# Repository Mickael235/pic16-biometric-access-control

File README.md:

# PIC16 Biometric Access Control

<p align="center">
  <strong>Biometric access-control system combining embedded electronics, PCB design and parametric mechanical integration</strong><br>
  PIC16F88 · SFM3050-TC1 · MAX232 · RS232 · Relays · KiCad · SolidWorks
</p>

<p align="center">
  <strong>Academic mechatronics project — ENSIM · Le Mans University · 2025</strong>
</p>

---

## Overview

This project focuses on the design of a **biometric access-control system** based on fingerprint authentication.

The system was designed around:

- a **SFM3050-TC1 fingerprint module**;
- a **PIC16F88 microcontroller**;
- a **MAX232 serial interface**;
- two electromechanical relays for access-control outputs;
- visual status indicators;
- a custom **KiCad PCB**;
- a dedicated **parametric SolidWorks enclosure**.

The project covers both the **electronic architecture** and the **mechanical integration** of the complete device.

> **Project status**
>
> The electronic schematic, PCB routing, 3D PCB validation and parametric enclosure were completed digitally.  
> The PCB was **not physically manufactured**, and the enclosure was **not 3D-printed / machined** before the end of the project.

---

## Project objectives

The system was designed to provide:

- fingerprint-based authentication;
- access-control output through relays;
- visual feedback using LEDs;
- configuration through a DIP switch and push button;
- serial communication between the fingerprint module and the controller;
- external RS232 connectivity;
- regulated 5 V and 3.3 V power rails;
- mechanical protection and ergonomic access to external components.

---

## Design targets

The original specification defined the following targets:

| Requirement | Target |
|---|---|
| Biometric sensor | SFM3050-TC1 |
| Fingerprint capacity | Up to 255 fingerprints |
| Sensor resolution | 508 dpi |
| Authentication time | < 1 s target |
| Main controller | PIC16F88 |
| MCU clock | 4 MHz quartz |
| Serial interface | RS232 |
| External power supply | 6 V / 500 mA |
| Logic supply | 5 V |
| Biometric-module supply | 3.3 V |
| User feedback | LEDs |
| Access output | 2 relays |

These values correspond to the **design requirements and selected component capabilities**, not to a completed physical validation campaign.

---

# 1. System architecture

The system is divided into five main functional blocks:

```text
Fingerprint module
      │
      │ Serial communication
      ▼
   MAX232
      │
      ▼
  PIC16F88
   │   │   │
   │   │   ├── DIP switch / push button
   │   │
   │   ├────── LEDs
   │
   └────────── Relay drivers
                  │
                  ▼
            Access-control load
```

The PIC16F88 acts as the central controller and is intended to:

- receive identification data from the biometric module;
- interpret the authentication result;
- control the relay outputs;
- manage LEDs and user inputs;
- supervise the overall access-control logic.

---

# 2. Electronic design

The complete electronic schematic was designed in **KiCad**.

## Main electronic blocks

### SFM3050-TC1 biometric module

The fingerprint module provides:

- fingerprint acquisition;
- local biometric processing;
- internal fingerprint storage;
- serial communication;
- 3.3 V operation.

A custom KiCad symbol was created from the module documentation because the component was not available in the standard KiCad libraries.

### PIC16F88

The PIC16F88 is the main control element.

Its intended responsibilities are:

- serial data reception;
- authentication-result processing;
- relay control;
- LED control;
- DIP-switch and push-button management.

### MAX232

The MAX232 provides level conversion between the serial interface and RS232 voltage levels.

This allows communication between the biometric-control electronics and an external RS232 interface.

### Relay outputs

Two relays are included to control an external access device, such as:

- an electric lock;
- a door-opening mechanism;
- another low-voltage access-control load.

The relays are driven through transistor stages and protected with flyback diodes.

### Visual indicators

Multiple LEDs provide system-state feedback, for example:

```text
System ready
Authentication accepted
Authentication rejected
Relay / door state
```

---

# 3. Power architecture

The system is powered from an external **6 V / 500 mA supply**.

Two regulated rails are generated:

```text
6 V input
   │
   ├── 7805 ─────→ 5 V
   │               ├── PIC16F88
   │               └── MAX232
   │
   └── LE33 ─────→ 3.3 V
                   └── SFM3050-TC1
```

Decoupling and filtering capacitors were included around the regulators and active devices to improve supply stability.

---

# 4. PCB design

The PCB was routed in KiCad after assigning footprints to the complete schematic.

## Placement strategy

The PCB layout was organized to:

- keep the biometric module accessible;
- place the power regulators near the supply input;
- keep the crystal close to the PIC16F88;
- separate relay power sections from sensitive logic;
- keep critical signal paths short;
- provide access to the DIP switch and push button;
- preserve clear routing around the serial interface.

Both front and back copper layers are used where necessary to complete routing while maintaining a compact design.

---

## 3D PCB validation

KiCad's 3D viewer was used to verify component placement and mechanical compatibility.

This view was used to check:

- component orientation;
- component height and spacing;
- relay placement;
- connector access;
- switch accessibility;
- overall PCB / enclosure integration.

Additional external 3D models were associated with selected components to improve the mechanical representation.

---

# 5. Mechanical enclosure

A dedicated enclosure was designed in **SolidWorks 2024** to protect the electronics while keeping the user-facing elements accessible.

The enclosure is approximately:

```text
124 mm × 80 mm
```

and includes dedicated openings for:

- the SFM3050-TC1 fingerprint module;
- status LEDs;
- the push button;
- the DIP switch;
- the external power cable;
- external connectors.

---

## Parametric front design

The enclosure geometry was built from pilot sketches so that key dimensions could be modified without manually rebuilding the entire model.

Important dimensions include:

- biometric sensor opening: approximately **38 mm × 31 mm**;
- LED openings;
- push-button opening;
- DIP-switch opening;
- enclosure wall thickness;
- corner radius;
- connector access.

---

## Isometric enclosure view

The enclosure consists of upper and lower parts designed to fit together while maintaining access to the electronics and external interfaces.

---

# 6. Parametric mechanical design

The enclosure was developed using a master-sketch / equation-driven strategy.

The model includes:

- pilot sketches;
- extruded base geometry;
- shell operations;
- fillets;
- component cut-outs;
- assembly lip and groove;
- fixation bosses;
- repeated fastening features;
- equation-driven geometry.

This approach makes the design easier to adapt if the PCB dimensions or component positions change.

---

## Lip-and-groove assembly

The upper and lower enclosure sections use a **lip-and-groove interface** to improve positioning and assembly repeatability.

The design relationship follows the principle:

```text
groove thickness = shell thickness / 2 + assembly clearance
lip thickness    = shell thickness / 2
```

This creates a controlled mechanical clearance between both enclosure halves.

---

## Fixation bosses

Internal bosses were added to maintain mechanical alignment and provide stable fastening points.

Their dimensions and spacing are linked to the main enclosure geometry.

This means that when the master dimensions are changed, the fastening features update automatically.

---

# 7. Section-view validation

A section view was used to verify:

- alignment of the upper and lower enclosure sections;
- lip-and-groove engagement;
- internal clearance;
- fixation-boss alignment;
- absence of major geometric interference.

---

# 8. Mechanical robustness test

The parametric model was also tested by modifying master dimensions such as:

- enclosure height;
- corner radius;
- shell-related dimensions.

The goal was to verify that:

- dependent geometry updated correctly;
- fastening bosses remained aligned;
- the enclosure remained assemblable;
- no major SolidWorks feature conflicts were introduced.

This validation showed that the model was sufficiently parameterized to support later design changes.

---

# 9. Electronic / mechanical integration

One of the main objectives of the project was not only to design a PCB, but to consider the PCB and enclosure as a single mechatronic system.

The integration process considered:

```text
Electronic requirements
        +
Component dimensions
        +
Connector accessibility
        +
User interaction
        +
Mechanical protection
        ↓
Integrated enclosure + PCB concept
```

Particular attention was given to:

- the fingerprint-reader opening;
- LED visibility;
- access to the push button and DIP switch;
- connector positioning;
- cable routing;
- PCB fastening;
- enclosure assembly.

---

# 10. Project validation status

| Item | Status |
|---|---|
| Functional requirements | ✅ Defined |
| Electronic architecture | ✅ Defined |
| KiCad schematic | ✅ Completed |
| Custom SFM3050 symbol | ✅ Completed |
| Footprint assignment | ✅ Completed |
| PCB routing | ✅ Completed |
| PCB 3D inspection | ✅ Completed |
| Parametric enclosure | ✅ Completed |
| Mechanical section checks | ✅ Completed |
| Parametric robustness tests | ✅ Completed |
| PCB manufacturing | ❌ Not completed |
| Physical enclosure fabrication | ❌ Not completed |
| Full physical system integration | ❌ Not completed |
| Firmware source in this repository | ❌ Not included |

The repository therefore documents a **complete electronic and mechanical design study**, rather than claiming a fabricated and experimentally validated final product.

---

# 11. Repository structure

```text
pic16-biometric-access-control/
│
├── README.md
├── .gitignore
│
├── assets/
│   └── images/
│       ├── pcb-3d-view.png
│       ├── pcb-layout.png
│       ├── schematic.png
│       ├── enclosure-front.png
│       ├── enclosure-isometric.png
│       └── enclosure-section.png
│
├── docs/
│   ├── electronics-report.pdf
│   └── mechanical-report.pdf
│
└── hardware/
    ├── electronics/
    │   ├── kicad/
    │   │   ├── biometric-access-control.kicad_pro
    │   │   ├── biometric-access-control.kicad_sch
    │   │   └── biometric-access-control.kicad_pcb
    │   │
    │   └── libraries/
    │       ├── symbols/
    │       │   └── SFM3050.kicad_sym
    │       ├── footprints/
    │       │   └── SW_DIP_x04.pretty/
    │       └── 3d-models/
    │
    └── mechanical/
        └── solidworks/
            └── Biometrique_Boitier.SLDASM
```

> SolidWorks part files should also be added under `hardware/mechanical/solidworks/` if the original `.SLDPRT` files are available.

---

# 12. Technologies

### Embedded / electronics

`PIC16F88` · `SFM3050-TC1` · `MAX232` · `RS232` · `Relays` · `LEDs`

### Electronic design

`KiCad` · `Schematic capture` · `PCB routing` · `Footprint assignment` · `3D PCB validation`

### Mechanical design

`SolidWorks 2024` · `Parametric CAD` · `Master sketches` · `Shell` · `Assembly features`

### Mechatronics

`Electronic / mechanical integration` · `Component accessibility` · `Enclosure design`

---

# 13. Engineering skills demonstrated

This project demonstrates experience with:

- electronic-system architecture;
- microcontroller-based system design;
- serial communication architecture;
- power-supply design;
- relay-driver design;
- schematic capture;
- custom KiCad symbols;
- PCB component placement;
- PCB routing;
- mechanical / electronic co-design;
- parametric SolidWorks modeling;
- tolerance and assembly considerations;
- technical documentation.

---

# 14. Documentation

The complete project documentation is available in:

### [Electronic design report](docs/electronics-report.pdf)

Covers:

- functional requirements;
- electronic architecture;
- PIC16F88;
- SFM3050-TC1;
- MAX232;
- relay outputs;
- power regulation;
- schematic design;
- custom biometric-module symbol;
- footprint assignment;
- PCB routing;
- 3D PCB inspection.

### [Mechanical design report](docs/mechanical-report.pdf)

Covers:

- enclosure requirements;
- pilot sketches;
- parametric modeling;
- upper and lower enclosure design;
- lip / groove assembly;
- fixation bosses;
- component openings;
- section-view validation;
- robustness tests.

---

# 15. Limitations and future work

The next steps required to transform this digital prototype into a complete physical system are:

1. **Manufacture the PCB**
   - produce Gerber files;
   - fabricate and assemble the board;
   - verify power rails and continuity.

2. **Develop / integrate firmware**
   - implement PIC16F88 serial communication;
   - interface the SFM3050-TC1;
   - implement authentication states;
   - drive LEDs and relays.

3. **Fabricate the enclosure**
   - 3D print or machine the housing;
   - validate clearances and connector accessibility;
   - test mechanical robustness.

4. **Perform complete system validation**
   - fingerprint enrollment;
   - successful / rejected authentication;
   - relay actuation;
   - long-term power and thermal testing.

5. **Improve user interaction**
   - optional buzzer;
   - richer status indication;
   - optional display or external supervision.

---

# Project outcome

This project resulted in a complete **digital mechatronic design** for a biometric access-control device combining:

- fingerprint-based access architecture;
- PIC16F88 control;
- RS232 interfacing;
- regulated power supplies;
- relay outputs;
- custom PCB design;
- 3D PCB validation;
- parametric enclosure design;
- mechanical integration studies.

Although the hardware was not fabricated, the project established a coherent architecture and validated the electronic and mechanical feasibility of the concept.

---

## Authors

**Michael Essomba**  
**Arsène Nguenang Youkap**

ENSIM — Le Mans University  
Academic year: **2024–2025**

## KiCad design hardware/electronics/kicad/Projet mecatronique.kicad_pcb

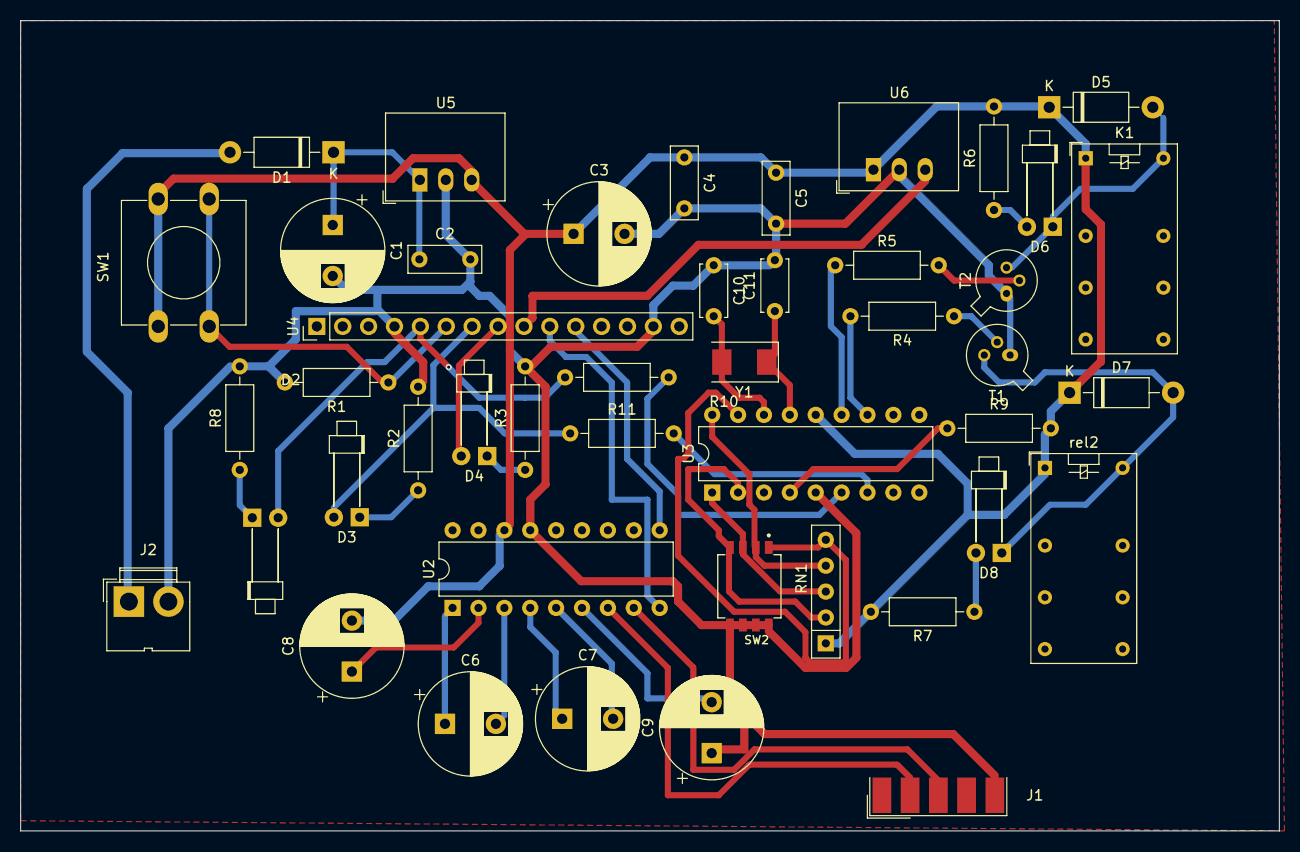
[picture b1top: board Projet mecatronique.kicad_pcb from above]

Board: 2 copper layers, 123.5 x 79.5 mm, 45 parts (0 on the bottom side), 38 nets.

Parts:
C1: 100µF; CP_Radial_D10.0mm_P5.00mm
C2, C4, C5: 100nF; C_Rect_L7.0mm_W2.5mm_P5.00mm
C3: 470µF; CP_Radial_D10.0mm_P5.00mm
C6, C7, C8, C9: 10µF; CP_Radial_D10.0mm_P5.00mm
C10, C11: 15pF; C_Disc_D5.0mm_W2.5mm_P5.00mm
D1, D5, D7: 1N4007; D_DO-41_SOD81_P10.16mm_Horizontal
D2, D3, D4, D6, D8: LED; LED_D1.8mm_W1.8mm_H2.4mm_Horizontal_O6.35mm_Z1.6mm
J1: DE9_Plug; DSUB-9_Female_EdgeMount_P2.77mm
J2: Conn_01x02_Pin; JWT_A3963_1x02_P3.96mm_Vertical
K1: G5V-2_Split; Relay_DPDT_Omron_G5V-2
R1, R2, R3, R8: 470; R_Axial_DIN0207_L6.3mm_D2.5mm_P10.16mm_Horizontal
R4, R5, R6, R7: 4.7k; R_Axial_DIN0207_L6.3mm_D2.5mm_P10.16mm_Horizontal
R9: 1k; R_Axial_DIN0207_L6.3mm_D2.5mm_P10.16mm_Horizontal
R10, R11: 220; R_Axial_DIN0207_L6.3mm_D2.5mm_P10.16mm_Horizontal
RN1: R_Network04; R_Array_SIP5
SW1: SW_Push; SW_PUSH-12mm
SW2: SW_DIP_x04
T1, T2: BC108; TO-18-3
U2: MAX232; DIP-18_W7.62mm
U3: PIC16F88-IP; DIP-18_W7.62mm
U4: PinHeader_1x15_P2.54mm_Vertical
U5: R-78E5.0-0.5; Converter_DCDC_RECOM_R-78E-0.5_THT
U6: R-783.3-0.5; Converter_DCDC_RECOM_R-78E-0.5_THT
Y1: Crystal; Crystal_SMD_0603-2Pin_6.0x3.5mm
rel2: G5V-2_Split; Relay_DPDT_Omron_G5V-2

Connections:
/3.3V: U4.9 (VDD), U6.3 (OUT)
/5V: C3.1, C4.1, C5.1, C8.2, D5.1 (K), D7.1 (K), K1.1, R6.2, R7.2, R9.2, RN1.1 (common), SW1.1, U2.16 (VCC), U3.14 (VDD), U5.3 (OUT), U6.1 (IN), rel2.1
/RA1: RN1.4 (R3), SW2.2, U3.18 (AN1/RA1)
/RA2: RN1.3 (R2), SW2.3, U3.1 (Vref-/CVref/AN2/RA2)
/RA3: RN1.2 (R1), SW2.4, U3.2 (C1OUT/Vref+/AN3/RA3)
/RB0: R10.1, U3.6 (RB0/INT/CCP1)
/RB1: R11.2, U3.7 (RB1/SDI/SDA)
/Rx: U2.9 (R2OUT), U4.10 (Rx)
/Tx: U2.10 (T2IN), U4.11 (Tx)
GND: C1.2, C2.2, C3.2, C4.2, C5.2, C9.1, C10.1, C11.2, J1.5, J2.2, R1.2, R2.2, R3.2, R8.2, RN1.5 (R4), SW2.1, SW2.1-1, SW2.2-1, SW2.3-1, SW2.4-1, T1.1 (E), T2.1 (E), U2.15 (GND), U3.5 (VSS), U3.17 (AN0/RA0), U4.4 (Vss), U4.14 (Vss), U5.2 (GND), U6.2 (GND)
unnamed: C1.1, C2.1, D1.1 (K), U5.1 (IN)
unnamed: D2.2 (A), R10.2, U4.5 (GPIO0)
unnamed: D2.1 (K), R8.1
unnamed: D3.2 (A), R11.1, U4.7 (GPIO2)
unnamed: D3.1 (K), R2.1
unnamed: D4.2 (A), U4.8 (GPIO3)
unnamed: D4.1 (K), R3.1
unnamed: D5.2 (A), D6.1 (K), K1.16, T2.3 (C)
unnamed: D6.2 (A), R6.1
unnamed: D7.2 (A), D8.1 (K), T1.3 (C), rel2.16
unnamed: D8.2 (A), R7.1
unnamed: R4.1, T1.2 (B)
unnamed: R5.2, T2.2 (B)
unnamed: C6.1, U2.1 (C1+)
unnamed: C6.2, U2.3 (C1-)
unnamed: C7.1, U2.4 (C2+)
unnamed: C7.2, U2.5 (C2-)
unnamed: J1.3, U2.8 (R2IN)
unnamed: J1.2, U2.7 (T2OUT)
unnamed: C8.1, U2.2 (VS+)
unnamed: C9.2, U2.6 (VS-)
unnamed: C10.2, U3.16 (CLKIN/OSC1/RA7), Y1.2
unnamed: C11.1, U3.15 (CLKOUT/OSC2/RA6), Y1.1
unnamed: R4.2, U3.12 (RB6/AN5/PGC/T1CKI)
unnamed: R5.1, U3.13 (RB7/AN6/PGD/T1OSI)
unnamed: R9.1, U3.4 (~MCLR/Vpp/RA5)
unnamed: R1.1, SW1.2, U4.6 (GPIO1)
VDD: D1.2 (A), J2.1
